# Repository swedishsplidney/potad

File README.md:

```text
                                        dP                  dP
                                        88                  88
                    88d888b. .d8888b. d8888P .d8888b. .d888b88
                    88'  `88 88'  `88   88   88'  `88 88'  `88
                    88.  .88 88.  .88   88   88.  .88 88.  .88
                    88Y888P' `88888P'   dP   `88888P8 `88888P8
                    88
                    dP       portable, open-source, tool (for) all-in-one development!
```

POTAD (portable open-source tool (for) all-in-one development) is a small, battery-powered coding machine so you can develop and code on the fly!

### note: potad is currently still in development and is not complete yet :)

---

# overview:

potad is a custom, portable, folding handheld device intended to run neovim (and other development tools)

it runs a custom linux-based distro designed using buildroot for lightweight efficiency

### features:

* fully custom single board computer based around the allwinner h616
* custom buildroot linux distro
* folding form factor with collapsing mechanical keyboard and oled touchscreen
* pre-prepared nvim, git, make, and more

---

# software specs:

**core**
* custom C++17 PID 1 (`potad_init`): early mounts, signal handling, service supervision with backoff, graceful shutdown
* `potad-ctl` control socket (`status`, `services`, `poweroff`, `reboot`), root only
* sysV-style `/etc/init.d/S*` scripts and `/etc/rc.local`
* fstab mounting with retries for late block devices; clean unmount and read-only root on shutdown
* persistent clock for boards without an RTC; `mdev` hotplug

**system**
* buildroot-generated aarch64 linux kernel, busybox userland
* u-boot + extlinux boot configuration
* DHCP networking
* deparate persistent `/home` partiton

**env**
* cross-compiled neovim/lazyvim, git, make, and more

**toolin**
* `scripts/build-app.sh`: one-command build script that may or may not be good
  * `scripts/run-qemu.sh`: boot in QEMU to test stuff

software development led by SwedishSplidney

---

# build and run:

no pre-prepared `.iso` files are available yet, but you can run it locally:
> note: make sure your parent directory doesn't have spaces in it (buildroot will freak out)

* clone the repo:
  ```bash
  git clone https://github.com/swedishsplidney/potad.git
  cd potad
  ```

* build the os image:
  ```bash
  ./scripts/build-app.sh
  ```
> note: setting up buildroot can take a while!

* run in qemu:
  ```bash
  ./scripts/run-qemu.sh
  ```
* or, if you want to test u-boot you can run:
  ```bash
  ./scripts/run-qemu-uboot.sh
  ```
  * then to boot into potadOS, run the following inside the u-boot terminal:
    ```text
    setenv bootcmd "ext4load virtio 0:0 0x40400000 /boot/Image; booti 0x40400000 - ${fdtcontroladdr}"
    setenv bootargs "console=ttyAMA0 root=/dev/vda rw earlycon init=/sbin/potad_init"
    boot
    ```

---

# Hardware

POTAD features a bunch of honestly quite cool hardware. Being a fully featured SBC it can realistically be used to run a full linux distribution for whatever is desired! Of course, the primary use case of POTAD is on-the-go development, even with its own USB OTG ports!

<sup>(get it: USB on-the-go? i don't even know if there is OTG support but hey)</sup>

The following hardware is on the SBC.

### HARDWARE SPECIFICATIONS:
---

* The Allwinner H616 CPU
* 4GB LPDDR4X SDRAM (the Samsung K4UBE3D4AB-MGCL)
* A 16 cm x 8 cm touchscreen OLED
* A 32GB onboard eMMC (the Samsung KLMAG1JETD-B041)

Alongside the SBC's computational hardware is also:
* An SD Card slot
* WiFi
* 2x USB-C ports
* 2x USB-A ports
* exposed gpio
* A custom collapsing mechanical keyboard
* 5000mah Lithium Polimer battery

The keyboard parts are:
* Capacitors (1uF and 0.1uF)
* Switches
* Diodes
* Resistors
* Quad SPI flash
* Crystal Oscillator
* Resistors
* Small push button

All of this is encompassed in an 3d printed shell (ASA).

Seeing as this is an SBC, the schematic is quite huge, but I'll try to walk you through it.

#### RTL8723DS-CG

In the top left, you'll see the RTL8723DS-CG. 

The RTL is a WiFi chip, capable of up to 150mbps transfer speeds, on the 2.4 GHz spectrum. Not much more there is to say about it, I'm afraid, so onto the next. Well, other than the fact that it is a six-by-six millimetre 48-pin WFQFM.

| Schematic | Real-life |
|:---:|:---:|
|  |  |

#### Samsung K4UBE3D4AB-MGCL

Next up is Samsung's K4UBE3D4AB-MGCL. The K4 is a 32 Gigabit / 4GB LPDDR4X SDRAM mobile memory integrated circuit manufactured by Samsung. It boasts a data rate up to 4266 Mbps at a clock frequency of 2.133 GHz.

Probably the most annoying thing about this chip has got to be the fact that it has 200 balls in a 10 x 15 mm FBGA package. This results in it having such a huge schematic symbol, which is just really a pain to work with.
  
| Schematic | Real-life |
|:---:|:---:|
|  |  |

Here's a real-life picture of how the ram looks. Keep in mind that on the wider side its *just 1.5 cm* and on the shorter side *approximately one centimetre*.

#### Samsung KLMAG1JETD-B041

Eh, two Samsungs in a row? Well, I guess yeah, but this Samsung KLMAG1JETD-B041 serves a completely different purpose than the last one. The KLM is a 16 GB, not gigabit but gigabyte, eMMC. eMMCs are non-volatile NAND flashes. They are quite similar to SSDs, as in they have no moving parts, but eMMCs have a much lower transfer speed, unfortunately, compared to SSDs. The other side of that is that it's much easier to route a slower chip. No need to worry about picoseconds, just nanoseconds.

Hence, you can see there are far, far fewer pins connected for data transfer, and most of the pins are just No Connect or for power.

Here's a real chip as well.

| Schematic | Real-life |
|:---:|:---:|
|  |  |

Note that this 153-ball FBGA package is just 11.5 x 13 mm, meaning on both sides it's just barely more than *one individual centimetre*.

#### TFP401PZP

Next up is Texas Instruments' TFP401PZP, a display driver. Google says its a "DVI (Digital Visual Interface) 1.0-compliant digital receiver and deserializer IC" whatever that is. ~~Let me get back to you after researching this.~~

So apparently it's a DVI interface IC. Why we have that, I know not, but hey that's cool!

Compared to the other ICs, the TFP is much bigger, at 14 x 14 mm, and well yeah! Here's a real life photo!

| Schematic | Real-life |
|:---:|:---:|
|  |  |

Well, yeah as you can see it actually has leads and stuff which is part of the reason why it's almost 1.5 x 1.5 cm in size.

#### USB

And of course, we have USB ports because they are super nice, two of each type!

Definitely has got to be the simplest part because of how universal they are!

<sub> Hardware design was led by FlyingFish, accompanied by Madhav and Kush. </sub>

#### Keyboard

Honestly, the schematic of the keyboard is pretty straightforward.

The crystal oscillator provides a highly stable signal for the RP2040. 

For the flash, some chips already come with flash, while others don't. In the RP2040's case, it does not have a flash, so we have to add our own. A simple way to think of a flash is a type of storage that is faster than the HDD, and consumes low power and higher reliability.

To learn more, look at the following [guide from HackClub](https://kaipereira.com/journal/build-a-devboard) itself!

These are some pictures of POTAD's keyboard!

<details>
  <summary>Schematic</summary>

| Actual keyboard itself |
|:---:|
|  |

| RP2040 | Quad SPI Flash | Crystal Oscillator |
|:---:|:---:|:---:|
|  |  |  | 
</details>

<details>
  <summary>2D PCB</summary>
  
| Function keys | Arrow keys + some more |
|:---:|:---:|
|  |  |

| Main middle keyboard |
|:---:|
|  |
</details>

<details>
  <summary>3D View</summary>
  
| Function keys | Arrow keys + some more |
|:---:|:---:|
|  |  |

| Main middle keyboard |
|:---:|
|  |
</details>
---

# license

POTAD is licensed under the GPLv3 licence

Check out `LICENCE.md` for more information

---

built by **FlyingFish**, **SwedishSplidney**, **Madhav**, and **Kus001**

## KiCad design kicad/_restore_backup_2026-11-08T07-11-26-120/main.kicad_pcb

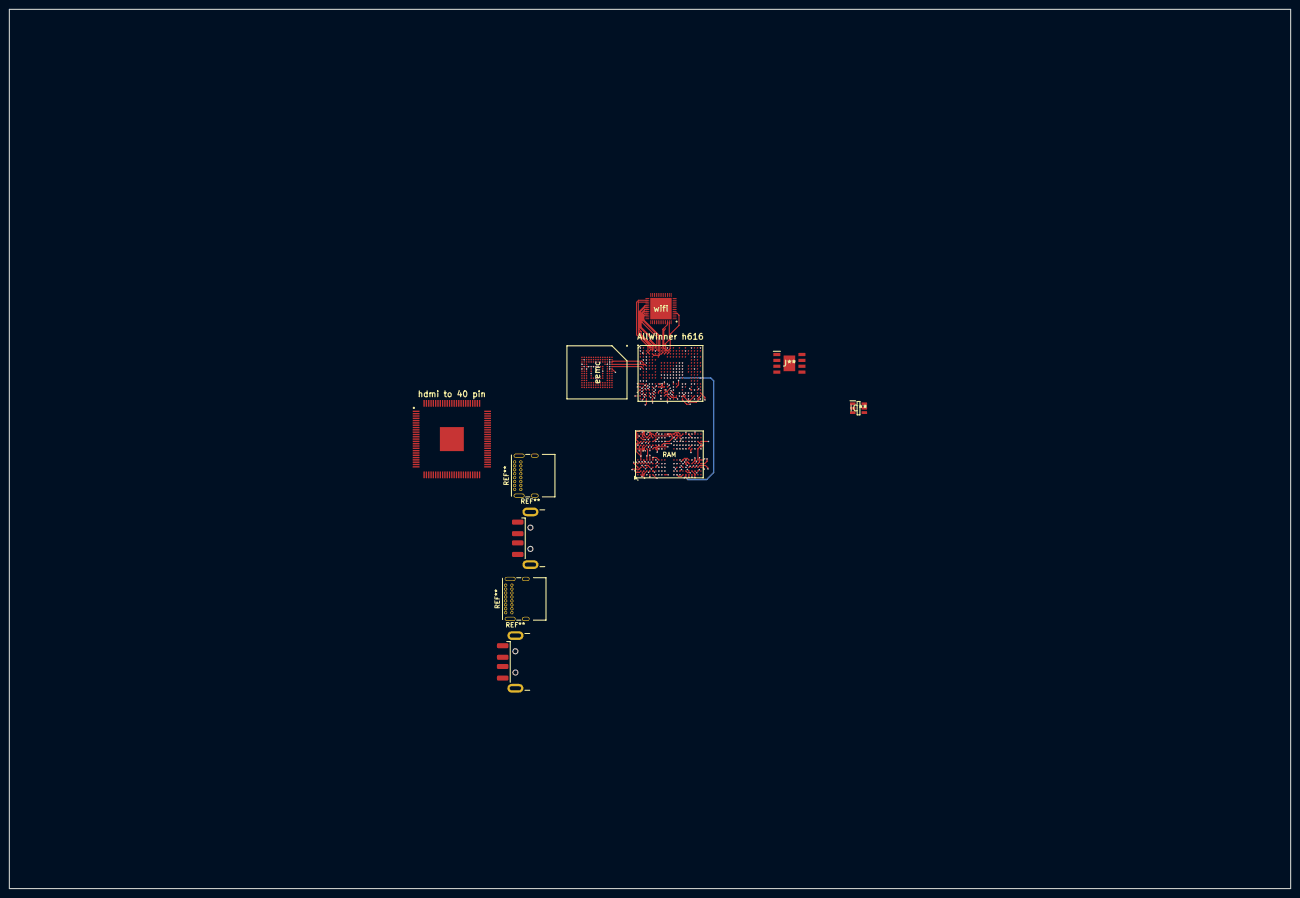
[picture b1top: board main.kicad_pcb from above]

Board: 8 copper layers, 277.2 x 190.2 mm, 7 parts (0 on the bottom side), 98 nets.

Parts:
AllWinner h616: BGA284C65P21X18_1400X1200X133
IC**: SOT95P280X145-6N
J**: thing
RAM: FBGA-200_L14.5-W10.0_RS1G32LF4D2BDS-53BT
eemc: BGA153C50P14X14_1150X1300X90
hdmi to 40 pin: QFP50P1600X1600X120-101N
wifi: QFN40P600X600X100-49N

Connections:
EMMC_3.3v: eemc.E6, eemc.F5, eemc.J10, eemc.K9
GND: AllWinner h616.A1, AllWinner h616.A10, AllWinner h616.A18, AllWinner h616.A21, AllWinner h616.B6, AllWinner h616.B16, AllWinner h616.D19, AllWinner h616.F14, AllWinner h616.F15, AllWinner h616.G13, AllWinner h616.G14, AllWinner h616.G15, AllWinner h616.H10, AllWinner h616.H11, AllWinner h616.H12, AllWinner h616.H13, AllWinner h616.H14, AllWinner h616.H15, AllWinner h616.H19, AllWinner h616.J12, AllWinner h616.J13, AllWinner h616.J14, AllWinner h616.J15, AllWinner h616.K8, AllWinner h616.K9, AllWinner h616.K10, AllWinner h616.K11, AllWinner h616.K12, AllWinner h616.K13, AllWinner h616.K14, AllWinner h616.K15, AllWinner h616.L21, AllWinner h616.M1, AllWinner h616.M2, AllWinner h616.M3, AllWinner h616.N6, AllWinner h616.N9, AllWinner h616.N12, AllWinner h616.N15, AllWinner h616.N18, AllWinner h616.P3, AllWinner h616.R5, AllWinner h616.R21, AllWinner h616.T1, AllWinner h616.T3, AllWinner h616.T8, AllWinner h616.T10, AllWinner h616.T15, AllWinner h616.T17, AllWinner h616.U6, AllWinner h616.U13, AllWinner h616.V1, AllWinner h616.V5, AllWinner h616.V12, AllWinner h616.V19, AllWinner h616.V21, RAM.A3, RAM.A10, RAM.AB3, RAM.AB5, RAM.AB8, RAM.AB10, RAM.C1, RAM.C5, RAM.C8, RAM.C12, RAM.D2, RAM.D4, RAM.D9, RAM.D11, RAM.E1, RAM.E5, RAM.E8, RAM.E12, RAM.G1, RAM.G3, RAM.G5, RAM.G8, RAM.G10, RAM.G12, RAM.J1, RAM.J3, RAM.J10, RAM.J12, RAM.K2, RAM.K4, RAM.K9, RAM.K11, RAM.N2, RAM.N4, RAM.N9, RAM.N11, RAM.P1, RAM.P3, RAM.P10, RAM.P12, RAM.T1, RAM.T3, RAM.T5, RAM.T8, RAM.T10, RAM.T12, RAM.V1, RAM.V5, RAM.V8, RAM.V12, RAM.W2, RAM.W4, RAM.W9, RAM.W11, RAM.Y1, RAM.Y5, RAM.Y8, RAM.Y12, eemc.A6, eemc.C4, eemc.E7, eemc.G5, eemc.H10, eemc.J5, eemc.K8, eemc.N2, eemc.N5, eemc.P4, eemc.P6
PC0: AllWinner h616.B1, eemc.H5
PC1: AllWinner h616.C2, eemc.K5
PC5: AllWinner h616.D3, eemc.M6
PC6: AllWinner h616.E2, eemc.M5
PC8: AllWinner h616.E3, eemc.B2
PC9: AllWinner h616.F1, eemc.B3
PC10: AllWinner h616.F2, eemc.A3
PC11: AllWinner h616.F3, eemc.B4
PC13: AllWinner h616.G3, eemc.A4
PC14: AllWinner h616.H1, eemc.B5
PC15: AllWinner h616.H2, eemc.A5
PC16: AllWinner h616.H3, eemc.B6
PG0: AllWinner h616.A6, wifi.31
PG1: AllWinner h616.C7, wifi.32
PG2: AllWinner h616.C6, wifi.30
PG3: AllWinner h616.B5, wifi.29
PG4: AllWinner h616.C5, wifi.34
PG5: AllWinner h616.B7, wifi.33
PG6: AllWinner h616.A4, wifi.27
PG7: AllWinner h616.B4, wifi.25
PG8: AllWinner h616.C4, wifi.26
PG10: AllWinner h616.C8, wifi.46
PG11: AllWinner h616.B10, wifi.47
PG12: AllWinner h616.C9, wifi.43
PG13: AllWinner h616.C10, wifi.4
SA0: AllWinner h616.T21, RAM.H2
SA1: AllWinner h616.U17, RAM.J2
SA2: AllWinner h616.T18, RAM.H9
SA3: AllWinner h616.T16, RAM.H10
SA4: AllWinner h616.R18, RAM.H11
SA5: AllWinner h616.P15, RAM.J11
SA6: AllWinner h616.U20, RAM.R2
SA7: AllWinner h616.N19, RAM.P2
SA8: AllWinner h616.U19, RAM.R9
SA9: AllWinner h616.N16, RAM.R10
SA10: AllWinner h616.R19, RAM.R11
SA11: AllWinner h616.U15, RAM.P11
SCKE0: AllWinner h616.V15, RAM.J4
SCKE1: AllWinner h616.P13, RAM.P4
SCKN: AllWinner h616.U14, RAM.J9, RAM.P9
SCKP: AllWinner h616.T14, RAM.J8, RAM.P8
SCS0: AllWinner h616.V17, RAM.H3
SCS1: AllWinner h616.R20, RAM.R3
SDQ0: AllWinner h616.N3, RAM.B2
SDQ1: AllWinner h616.U4, RAM.C2
SDQ2: AllWinner h616.N2, RAM.E2
SDQ3: AllWinner h616.T4, RAM.F2
SDQ4: AllWinner h616.U3, RAM.F4
SDQ5: AllWinner h616.P1, RAM.E4
SDQ6: AllWinner h616.T2, RAM.C4
SDQ7: AllWinner h616.P2, RAM.B4
SDQ8: AllWinner h616.P5, RAM.B11
SDQ9: AllWinner h616.V3, RAM.C11
SDQ10: AllWinner h616.P4, RAM.E11
SDQ11: AllWinner h616.R4, RAM.F11
SDQ12: AllWinner h616.R6, RAM.F9
SDQ13: AllWinner h616.N4, RAM.E9
SDQ14: AllWinner h616.P6, RAM.C9
SDQ15: AllWinner h616.N5, RAM.B9
SDQ16: AllWinner h616.T11, RAM.AA2
SDQ17: AllWinner h616.U12, RAM.Y2
SDQ18: AllWinner h616.T12, RAM.V2
SDQ19: AllWinner h616.U9, RAM.U2
SDQ20: AllWinner h616.T6, RAM.U4
SDQ21: AllWinner h616.U5, RAM.V4
SDQ22: AllWinner h616.T7, RAM.Y4
SDQ23: AllWinner h616.T5, RAM.AA4
SDQ24: AllWinner h616.R9, RAM.AA11
SDQ25: AllWinner h616.P7, RAM.Y11
SDQ26: AllWinner h616.N7, RAM.V11
SDQ27: AllWinner h616.P9, RAM.U11
SDQ28: AllWinner h616.P10, RAM.U9
SDQ29: AllWinner h616.U11, RAM.V9
SDQ30: AllWinner h616.P12, RAM.Y9
SDQ31: AllWinner h616.R12, RAM.AA9
SDQM0: AllWinner h616.U1, RAM.C3
SDQM1: AllWinner h616.R3, RAM.C10
SDQM2: AllWinner h616.T9, RAM.Y3
SDQM3: AllWinner h616.N10, RAM.Y10
SDQS0N: AllWinner h616.R1, RAM.E3
SDQS0P: AllWinner h616.R2, RAM.D3
SDQS1N: AllWinner h616.V2, RAM.E10
SDQS1P: AllWinner h616.U2, RAM.D10
SDQS2N: AllWinner h616.U8, RAM.V3
SDQS2P: AllWinner h616.V8, RAM.W3
SDQS3N: AllWinner h616.U10, RAM.V10
SDQS3P: AllWinner h616.V10, RAM.W10
SRST: AllWinner h616.U21, RAM.T11
VCCQ_DRAM: RAM.AA3, RAM.AA5, RAM.AA8, RAM.AA10, RAM.B3, RAM.B5, RAM.B8, RAM.B10, RAM.D1, RAM.D5, RAM.D8, RAM.D12, RAM.F3, RAM.F10, RAM.U3, RAM.W1, RAM.W5, RAM.W8, RAM.W12
VCC_DRAM: AllWinner h616.L9, AllWinner h616.L10, AllWinner h616.L11, AllWinner h616.L12, AllWinner h616.L13, RAM.A4, RAM.A9, RAM.AB4, RAM.AB9, RAM.F5, RAM.F8, RAM.H1, RAM.H5, RAM.H8, RAM.H12, RAM.K1, RAM.K3, RAM.K10, RAM.K12, RAM.N1, RAM.N3, RAM.N10, RAM.N12, RAM.R1, RAM.R5, RAM.R8, RAM.R12, RAM.U5, RAM.U8
VCC_PC: AllWinner h616.F5, eemc.C6, eemc.M4, eemc.N4, eemc.P3, eemc.P5
VDD18_DRAM: AllWinner h616.L14, RAM.F1, RAM.F12, RAM.G4, RAM.G9, RAM.T4, RAM.T9, RAM.U1, RAM.U12
VDD_CPU: AllWinner h616.H8, AllWinner h616.H9, AllWinner h616.J8, AllWinner h616.J9, AllWinner h616.J10, AllWinner h616.J11
VDD_GPU: AllWinner h616.F9, AllWinner h616.F10, AllWinner h616.G8, AllWinner h616.G9
VDD_SYS: AllWinner h616.F11, AllWinner h616.F12, AllWinner h616.F13, AllWinner h616.G10, AllWinner h616.G11, AllWinner h616.G12
antana: wifi.11, wifi.48

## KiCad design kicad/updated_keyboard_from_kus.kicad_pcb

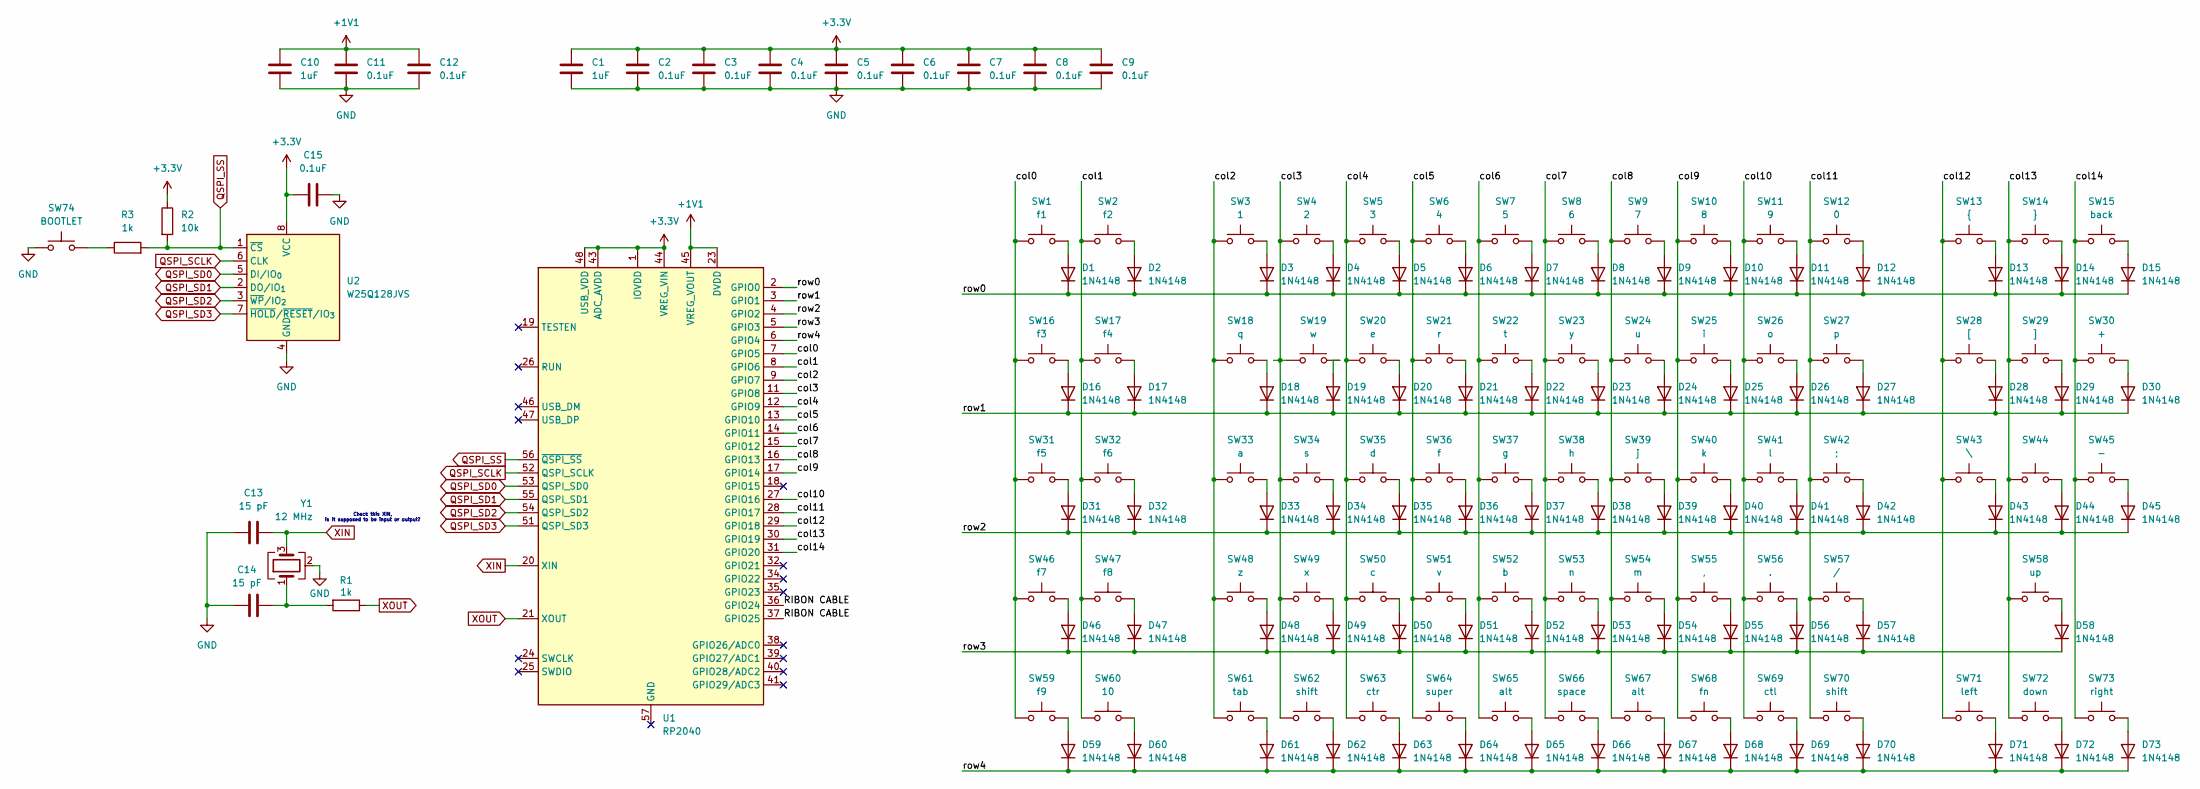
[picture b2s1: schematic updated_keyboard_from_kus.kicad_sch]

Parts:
C1, C10: 1uF; C_0402_1005Metric
C2, C3, C4, C5, C6, C7, C8, C9, C11, C12, C15: 0.1uF; C_0402_1005Metric
C13, C14: 15 pF; C_0402_1005Metric
D1, D2, D3, D4, D5, D6, D7, D8, D9, D10, D11, D12, D13, D14, D15, D16, D17, D18, D19, D20, D21, D22, D23, D24, D25, D26, D27, D28, D29, D30, D31, D32, D33, D34, D35, D36, D37, D38, D39, D40, D41, D42, D43, D44, D45, D46, D47, D48, D49, D50, D51, D52, D53, D54, D55, D56, D57, D58, D59, D60, D61, D62, D63, D64, D65, D66, D67, D68, D69, D70, D71, D72, D73: 1N4148; D_DO-35_SOD27_P7.62mm_Horizontal
R1, R3: 1k; R_0402_1005Metric
R2: 10k; R_0402_1005Metric
SW1: f1; SW_Push_1P1T_NO_CK_PTS125Sx43PSMTR
SW2: f2; SW_Push_1P1T_NO_CK_PTS125Sx43PSMTR
SW3: 1; SW_Push_1P1T_NO_CK_PTS125Sx43PSMTR
SW4: 2; SW_Push_1P1T_NO_CK_PTS125Sx43PSMTR
SW5: 3; SW_Push_1P1T_NO_CK_PTS125Sx43PSMTR
SW6: 4; SW_Push_1P1T_NO_CK_PTS125Sx43PSMTR
SW7: 5; SW_Push_1P1T_NO_CK_PTS125Sx43PSMTR
SW8: 6; SW_Push_1P1T_NO_CK_PTS125Sx43PSMTR
SW9: 7; SW_Push_1P1T_NO_CK_PTS125Sx43PSMTR
SW10: 8; SW_Push_1P1T_NO_CK_PTS125Sx43PSMTR
SW11: 9; SW_Push_1P1T_NO_CK_PTS125Sx43PSMTR
SW12: 0; SW_Push_1P1T_NO_CK_PTS125Sx43PSMTR
SW13: {; SW_Push_1P1T_NO_CK_PTS125Sx43PSMTR
SW14: }; SW_Push_1P1T_NO_CK_PTS125Sx43PSMTR
SW15: back; SW_Push_1P1T_NO_CK_PTS125Sx43PSMTR
SW16: f3; SW_Push_1P1T_NO_CK_PTS125Sx43PSMTR
SW17: f4; SW_Push_1P1T_NO_CK_PTS125Sx43PSMTR
SW18: q; SW_Push_1P1T_NO_CK_PTS125Sx43PSMTR
SW19: w; SW_Push_1P1T_NO_CK_PTS125Sx43PSMTR
SW20: e; SW_Push_1P1T_NO_CK_PTS125Sx43PSMTR
SW21: r; SW_Push_1P1T_NO_CK_PTS125Sx43PSMTR
SW22: t; SW_Push_1P1T_NO_CK_PTS125Sx43PSMTR
SW23: y; SW_Push_1P1T_NO_CK_PTS125Sx43PSMTR
SW24: u; SW_Push_1P1T_NO_CK_PTS125Sx43PSMTR
SW25: i; SW_Push_1P1T_NO_CK_PTS125Sx43PSMTR
SW26: o; SW_Push_1P1T_NO_CK_PTS125Sx43PSMTR
SW27: p; SW_Push_1P1T_NO_CK_PTS125Sx43PSMTR
SW28: [; SW_Push_1P1T_NO_CK_PTS125Sx43PSMTR
SW29: ]; SW_Push_1P1T_NO_CK_PTS125Sx43PSMTR
SW30: +; SW_Push_1P1T_NO_CK_PTS125Sx43PSMTR
SW31: f5; SW_Push_1P1T_NO_CK_PTS125Sx43PSMTR
SW32: f6; SW_Push_1P1T_NO_CK_PTS125Sx43PSMTR
SW33: a; SW_Push_1P1T_NO_CK_PTS125Sx43PSMTR
SW34: s; SW_Push_1P1T_NO_CK_PTS125Sx43PSMTR
SW35: d; SW_Push_1P1T_NO_CK_PTS125Sx43PSMTR
SW36: f; SW_Push_1P1T_NO_CK_PTS125Sx43PSMTR
SW37: g; SW_Push_1P1T_NO_CK_PTS125Sx43PSMTR
SW38: h; SW_Push_1P1T_NO_CK_PTS125Sx43PSMTR
SW39: j; SW_Push_1P1T_NO_CK_PTS125Sx43PSMTR
SW40: k; SW_Push_1P1T_NO_CK_PTS125Sx43PSMTR
SW41: l; SW_Push_1P1T_NO_CK_PTS125Sx43PSMTR
SW42: ;; SW_Push_1P1T_NO_CK_PTS125Sx43PSMTR
SW43: \; SW_Push_1P1T_NO_CK_PTS125Sx43PSMTR
SW44: SW_Push_1P1T_NO_CK_PTS125Sx43PSMTR
SW45: -; SW_Push_1P1T_NO_CK_PTS125Sx43PSMTR
SW46: f7; SW_Push_1P1T_NO_CK_PTS125Sx43PSMTR
SW47: f8; SW_Push_1P1T_NO_CK_PTS125Sx43PSMTR
SW48: z; SW_Push_1P1T_NO_CK_PTS125Sx43PSMTR
SW49: x; SW_Push_1P1T_NO_CK_PTS125Sx43PSMTR
SW50: c; SW_Push_1P1T_NO_CK_PTS125Sx43PSMTR
SW51: v; SW_Push_1P1T_NO_CK_PTS125Sx43PSMTR
SW52: b; SW_Push_1P1T_NO_CK_PTS125Sx43PSMTR
SW53: n; SW_Push_1P1T_NO_CK_PTS125Sx43PSMTR
SW54: m; SW_Push_1P1T_NO_CK_PTS125Sx43PSMTR
SW55: ,; SW_Push_1P1T_NO_CK_PTS125Sx43PSMTR
SW56: .; SW_Push_1P1T_NO_CK_PTS125Sx43PSMTR
SW57: /; SW_Push_1P1T_NO_CK_PTS125Sx43PSMTR
SW58: up; SW_Push_1P1T_NO_CK_PTS125Sx43PSMTR
SW59: f9; SW_Push_1P1T_NO_CK_PTS125Sx43PSMTR
SW60: 10; SW_Push_1P1T_NO_CK_PTS125Sx43PSMTR
SW61: tab; SW_Push_1P1T_NO_CK_PTS125Sx43PSMTR
SW62, SW70: shift; SW_Push_1P1T_NO_CK_PTS125Sx43PSMTR
SW63: ctr; SW_Push_1P1T_NO_CK_PTS125Sx43PSMTR
SW64: super; SW_Push_1P1T_NO_CK_PTS125Sx43PSMTR
SW65, SW67: alt; SW_Push_1P1T_NO_CK_PTS125Sx43PSMTR
SW66: space; SW_Push_1P1T_NO_CK_PTS125Sx43PSMTR
SW68: fn; SW_Push_1P1T_NO_CK_PTS125Sx43PSMTR
SW69: ctl; SW_Push_1P1T_NO_CK_PTS125Sx43PSMTR
SW71: left; SW_Push_1P1T_NO_CK_PTS125Sx43PSMTR
SW72: down; SW_Push_1P1T_NO_CK_PTS125Sx43PSMTR
SW73: right; SW_Push_1P1T_NO_CK_PTS125Sx43PSMTR
SW74: BOOTLET; SW_Push_SPST_NO_Alps_SKRK
U1: RP2040; QFN-56-1EP_7x7mm_P0.4mm_EP3.2x3.2mm
U2: W25Q128JVS; SOIC-8_5.3x5.3mm_P1.27mm
Y1: 12 MHz; Crystal_SMD_3225-4Pin_3.2x2.5mm

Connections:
+1V1: C10.1, C11.1, C12.1, U1.23 (DVDD), U1.45 (VREG_VOUT), U1.50 (DVDD)
+3.3V: C1.1, C2.1, C3.1, C4.1, C5.1, C6.1, C7.1, C8.1, C9.1, C15.1, R2.1, U1.1 (IOVDD), U1.10 (IOVDD), U1.22 (IOVDD), U1.33 (IOVDD), U1.42 (IOVDD), U1.43 (ADC_AVDD), U1.44 (VREG_VIN), U1.48 (USB_VDD), U1.49 (IOVDD), U2.8 (VCC)
/RIBON CABLE: U1.36 (GPIO24), U1.37 (GPIO25)
/col0: SW1.1, SW16.1, SW31.1, SW46.1, SW59.1, U1.7 (GPIO5)
/col1: SW2.1, SW17.1, SW32.1, SW47.1, SW60.1, U1.8 (GPIO6)
/col2: SW3.1, SW18.1, SW33.1, SW48.1, SW61.1, U1.9 (GPIO7)
/col3: SW4.1, SW19.1, SW34.1, SW49.1, SW62.1, U1.11 (GPIO8)
/col4: SW5.1, SW20.1, SW35.1, SW50.1, SW63.1, U1.12 (GPIO9)
/col5: SW6.1, SW21.1, SW36.1, SW51.1, SW64.1, U1.13 (GPIO10)
/col6: SW7.1, SW22.1, SW37.1, SW52.1, SW65.1, U1.14 (GPIO11)
/col7: SW8.1, SW23.1, SW38.1, SW53.1, SW66.1, U1.15 (GPIO12)
/col8: SW9.1, SW24.1, SW39.1, SW54.1, SW67.1, U1.16 (GPIO13)
/col9: SW10.1, SW25.1, SW40.1, SW55.1, SW68.1, U1.17 (GPIO14)
/col10: SW11.1, SW26.1, SW41.1, SW56.1, SW69.1, U1.27 (GPIO16)
/col11: SW12.1, SW27.1, SW42.1, SW57.1, SW70.1, U1.28 (GPIO17)
/col12: SW13.1, SW28.1, SW43.1, SW71.1, U1.29 (GPIO18)
/col13: SW14.1, SW29.1, SW44.1, SW58.1, SW72.1, U1.30 (GPIO19)
/col14: SW15.1, SW30.1, SW45.1, SW73.1, U1.31 (GPIO20)
/row0: D1.1 (K), D2.1 (K), D3.1 (K), D4.1 (K), D5.1 (K), D6.1 (K), D7.1 (K), D8.1 (K), D9.1 (K), D10.1 (K), D11.1 (K), D12.1 (K), D13.1 (K), D14.1 (K), D15.1 (K), U1.2 (GPIO0)
/row1: D16.1 (K), D17.1 (K), D18.1 (K), D19.1 (K), D20.1 (K), D21.1 (K), D22.1 (K), D23.1 (K), D24.1 (K), D25.1 (K), D26.1 (K), D27.1 (K), D28.1 (K), D29.1 (K), D30.1 (K), U1.3 (GPIO1)
/row2: D31.1 (K), D32.1 (K), D33.1 (K), D34.1 (K), D35.1 (K), D36.1 (K), D37.1 (K), D38.1 (K), D39.1 (K), D40.1 (K), D41.1 (K), D42.1 (K), D43.1 (K), D44.1 (K), D45.1 (K), U1.4 (GPIO2)
/row3: D46.1 (K), D47.1 (K), D48.1 (K), D49.1 (K), D50.1 (K), D51.1 (K), D52.1 (K), D53.1 (K), D54.1 (K), D55.1 (K), D56.1 (K), D57.1 (K), D58.1 (K), U1.5 (GPIO3)
/row4: D59.1 (K), D60.1 (K), D61.1 (K), D62.1 (K), D63.1 (K), D64.1 (K), D65.1 (K), D66.1 (K), D67.1 (K), D68.1 (K), D69.1 (K), D70.1 (K), D71.1 (K), D72.1 (K), D73.1 (K), U1.6 (GPIO4)
GND: C1.2, C2.2, C3.2, C4.2, C5.2, C6.2, C7.2, C8.2, C9.2, C10.2, C11.2, C12.2, C13.1, C14.1, C15.2, SW74.1, U2.4 (GND), Y1.2 (G), Y1.4 (G)
unnamed: C14.2, R1.2, Y1.1
unnamed: D1.2 (A), SW1.2
unnamed: D2.2 (A), SW2.2
unnamed: D3.2 (A), SW3.2
unnamed: D4.2 (A), SW4.2
unnamed: D5.2 (A), SW5.2
unnamed: D6.2 (A), SW6.2
unnamed: D7.2 (A), SW7.2
unnamed: D8.2 (A), SW8.2
unnamed: D9.2 (A), SW9.2
unnamed: D10.2 (A), SW10.2
unnamed: D11.2 (A), SW11.2
unnamed: D12.2 (A), SW12.2
unnamed: D13.2 (A), SW13.2
unnamed: D14.2 (A), SW14.2
unnamed: D15.2 (A), SW15.2
unnamed: D16.2 (A), SW16.2
unnamed: D17.2 (A), SW17.2
unnamed: D18.2 (A), SW18.2
unnamed: D19.2 (A), SW19.2
unnamed: D20.2 (A), SW20.2
unnamed: D21.2 (A), SW21.2
unnamed: D22.2 (A), SW22.2
unnamed: D23.2 (A), SW23.2
unnamed: D24.2 (A), SW24.2
unnamed: D25.2 (A), SW25.2
unnamed: D26.2 (A), SW26.2
unnamed: D27.2 (A), SW27.2
unnamed: D28.2 (A), SW28.2
unnamed: D29.2 (A), SW29.2
unnamed: D30.2 (A), SW30.2
unnamed: D31.2 (A), SW31.2
unnamed: D32.2 (A), SW32.2
unnamed: D33.2 (A), SW33.2
unnamed: D34.2 (A), SW34.2
unnamed: D35.2 (A), SW35.2
unnamed: D36.2 (A), SW36.2
unnamed: D37.2 (A), SW37.2
unnamed: D38.2 (A), SW38.2
unnamed: D39.2 (A), SW39.2
unnamed: D40.2 (A), SW40.2
unnamed: D41.2 (A), SW41.2
unnamed: D42.2 (A), SW42.2
unnamed: D43.2 (A), SW43.2
unnamed: D44.2 (A), SW44.2
unnamed: D45.2 (A), SW45.2
unnamed: D46.2 (A), SW46.2
unnamed: D47.2 (A), SW47.2
unnamed: D48.2 (A), SW48.2
unnamed: D49.2 (A), SW49.2
unnamed: D50.2 (A), SW50.2
unnamed: D51.2 (A), SW51.2
unnamed: D52.2 (A), SW52.2
unnamed: D53.2 (A), SW53.2
unnamed: D54.2 (A), SW54.2
unnamed: D55.2 (A), SW55.2
unnamed: D56.2 (A), SW56.2
unnamed: D57.2 (A), SW57.2
unnamed: D58.2 (A), SW58.2
unnamed: D59.2 (A), SW59.2
unnamed: D60.2 (A), SW60.2
unnamed: D61.2 (A), SW61.2
unnamed: D62.2 (A), SW62.2
unnamed: D63.2 (A), SW63.2
unnamed: D64.2 (A), SW64.2
unnamed: D65.2 (A), SW65.2
unnamed: D66.2 (A), SW66.2
unnamed: D67.2 (A), SW67.2
unnamed: D68.2 (A), SW68.2
unnamed: D69.2 (A), SW69.2
unnamed: D70.2 (A), SW70.2
unnamed: D71.2 (A), SW71.2
unnamed: D72.2 (A), SW72.2
unnamed: D73.2 (A), SW73.2
unnamed: R3.1, SW74.2
QSPI_SCLK: U1.52 (QSPI_SCLK), U2.6 (CLK)
QSPI_SD0: U1.53 (QSPI_SD0), U2.5 (DI/IO_{0})
QSPI_SD1: U1.55 (QSPI_SD1), U2.2 (DO/IO_{1})
QSPI_SD2: U1.54 (QSPI_SD2), U2.3 (~WP/IO_{2})
QSPI_SD3: U1.51 (QSPI_SD3), U2.7 (~HOLD/~RESET/IO_{3})
QSPI_SS: R2.2, R3.2, U1.56 (~QSPI_SS), U2.1 (~CS)
XIN: C13.2, U1.20 (XIN), Y1.3
XOUT: R1.1, U1.21 (XOUT)

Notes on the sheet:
Check this XIN, is it supposed to be input or output?

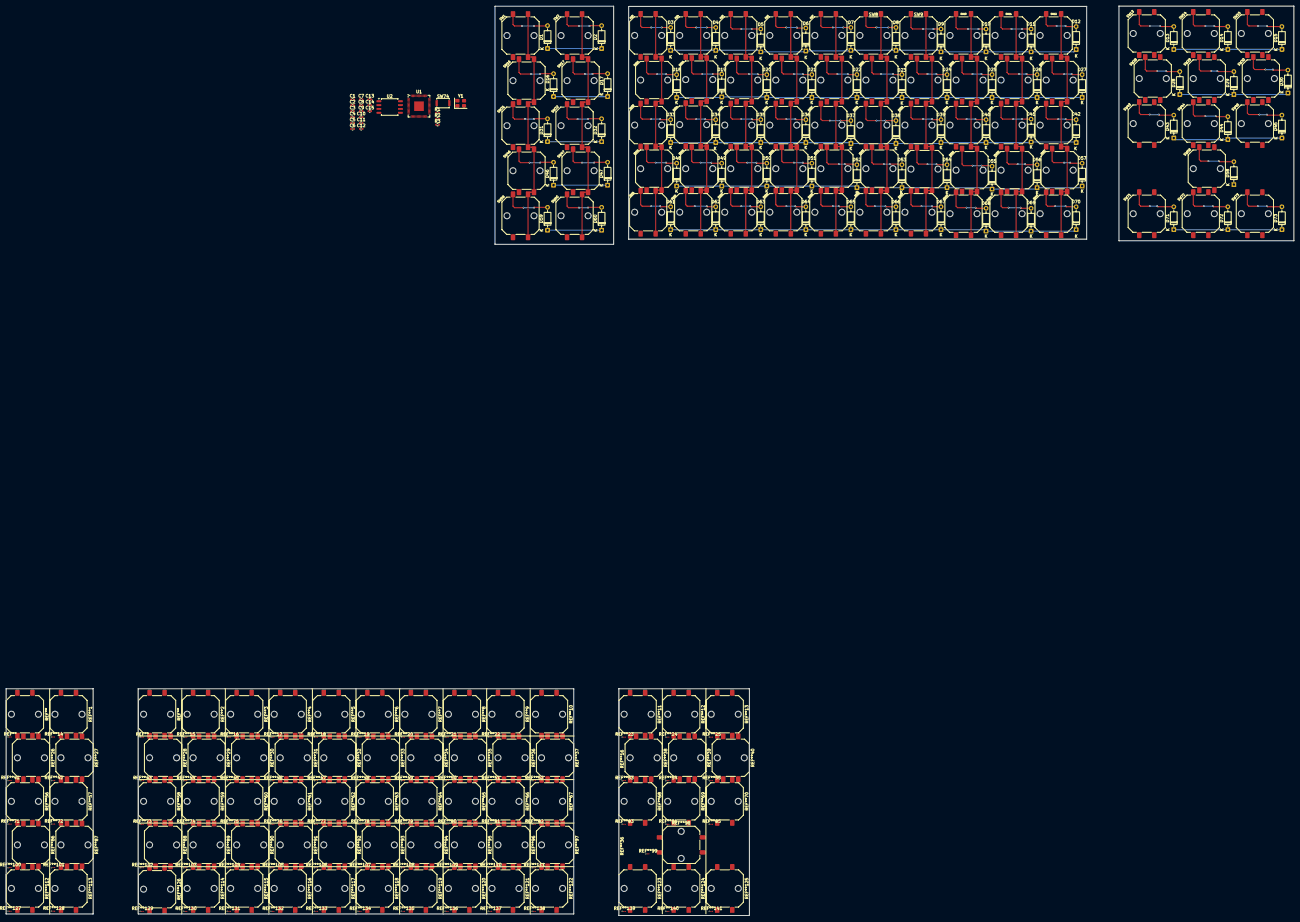
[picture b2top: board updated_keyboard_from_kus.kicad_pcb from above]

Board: 10 copper layers, 428.8 x 302.8 mm, 168 parts (0 on the bottom side), 107 nets.
